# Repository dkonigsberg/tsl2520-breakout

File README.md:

# TSL2520 Breakout Board

This repository contains the [KiCad](http://kicad.org/) project
with the complete circuit schematics and PCB layout for a breakout
board that supports a certain series of 1.8V light sensors from
[AMS](https://ams-osram.com/).

The supported selection of sensors all appear to be pin-compatible,
interface compatible, and only differ in minor ways. These sensors
include:

* [TSL2520](https://ams-osram.com/en/tsl2520) - Light sensor with Clear and IR channels
* [TSL2521](https://ams-osram.com/en/tsl2521) - Light sensor with Clear and IR channels, and flicker detection
* [TSL2522](https://ams-osram.com/en/tsl2522) - Light sensor with Photopic and IR channels, and flicker detection
* [TCS3410](https://ams-osram.com/en/tcs3410) - Light sensor with Color channels and flicker detection

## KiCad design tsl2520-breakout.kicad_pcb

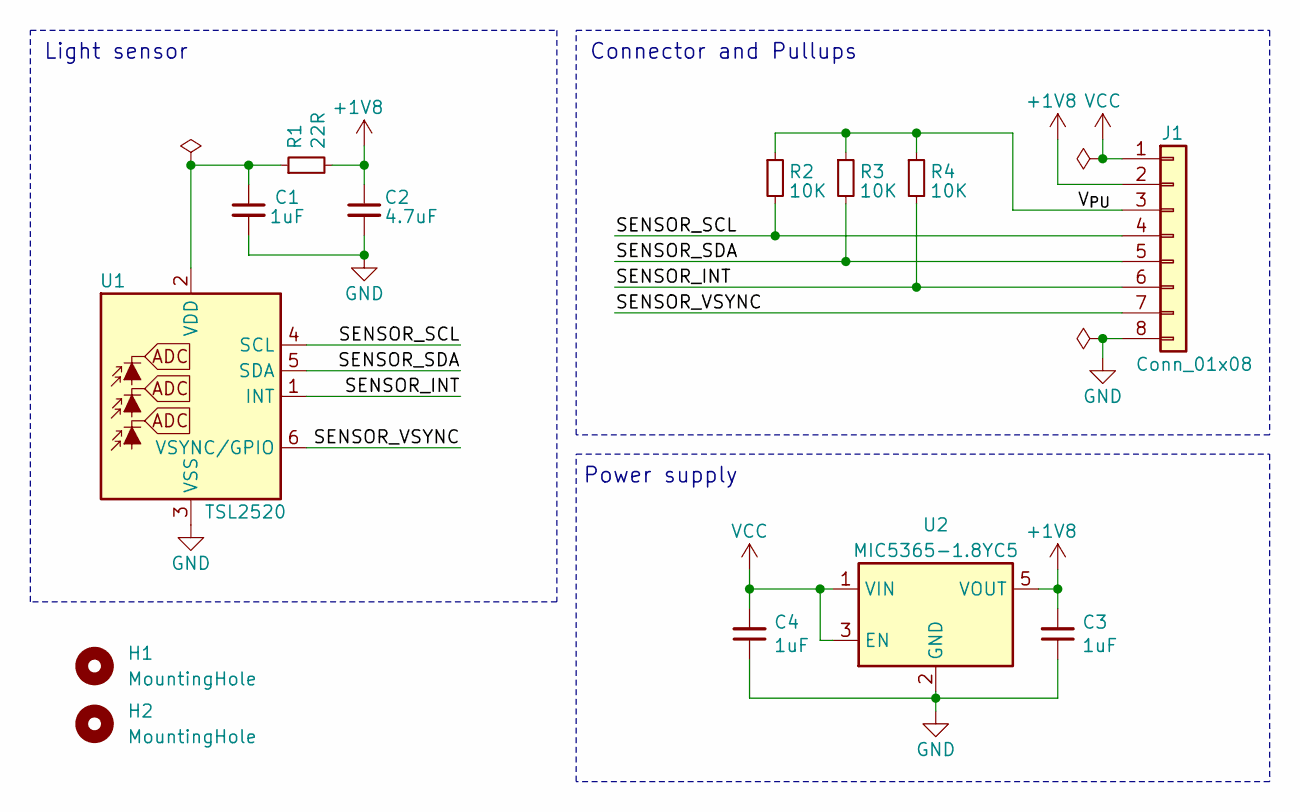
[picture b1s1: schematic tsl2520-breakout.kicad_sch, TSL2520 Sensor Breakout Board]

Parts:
C1: 1uF; C_0402_1005Metric; Manufacturer PN CL05A105KQ5NNNC
C2: 4.7uF; C_0402_1005Metric; Manufacturer PN CL05A475KQ5NRNC
C3, C4: 1uF; C_0603_1608Metric; Manufacturer PN CL10B105KA8NNNC
H1, H2: MountingHole; MountingHole_2.5mm_Pad
J1: Conn_01x08; PinHeader_1x08_P2.54mm_Vertical
R1: 22R; R_0402_1005Metric; Manufacturer PN AC0402JR-0722RL
R2, R3, R4: 10K; R_0603_1608Metric; Manufacturer PN CRCW060310K0JNEA
U1: TSL2520; AMS_TSL2585_OLGA-6_2x1mm_P0.65mm; Manufacturer PN TSL25203M
U2: MIC5365-1.8YC5; SOT-353_SC-70-5; Manufacturer PN MIC5365-1.8YC5-TR

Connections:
+1V8: C2.1, C3.2, J1.2, R1.2, U2.5 (VOUT)
/SENSOR_INT: J1.6, R4.2, U1.1 (INT)
/SENSOR_SCL: J1.4, R2.2, U1.4 (SCL)
/SENSOR_SDA: J1.5, R3.2, U1.5 (SDA)
/SENSOR_VSYNC: J1.7, U1.6 (VSYNC/GPIO)
/V_{PU}: J1.3, R2.1, R3.1, R4.1
GND: C1.2, C2.2, C3.1, C4.1, J1.8, U1.3 (VSS), U2.2 (GND)
unnamed: C1.1, R1.1, U1.2 (VDD)
VCC: C4.2, J1.1, U2.1 (VIN), U2.3 (EN)

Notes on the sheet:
Light sensor
Connector and Pullups
Power supply

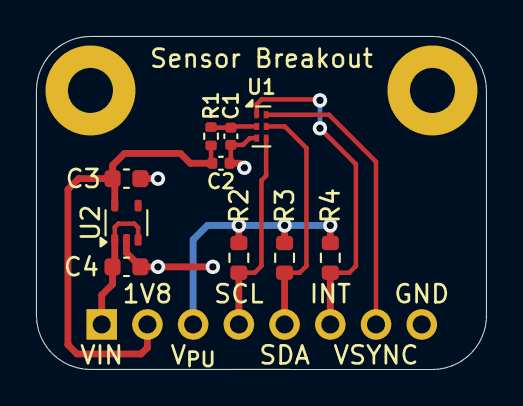
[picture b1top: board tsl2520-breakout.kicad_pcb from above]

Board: 2 copper layers, 25.0 x 18.5 mm, 13 parts (1 on the bottom side), 9 nets.

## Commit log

2023-12-05 Rename project files and identifiers
2023-12-05 Update symbol, schematic, and PCB layout
2023-12-05 Update images
2025-04-08 Update breakout board design
    Changes for KiCad v9 update and various silkscreen changes
